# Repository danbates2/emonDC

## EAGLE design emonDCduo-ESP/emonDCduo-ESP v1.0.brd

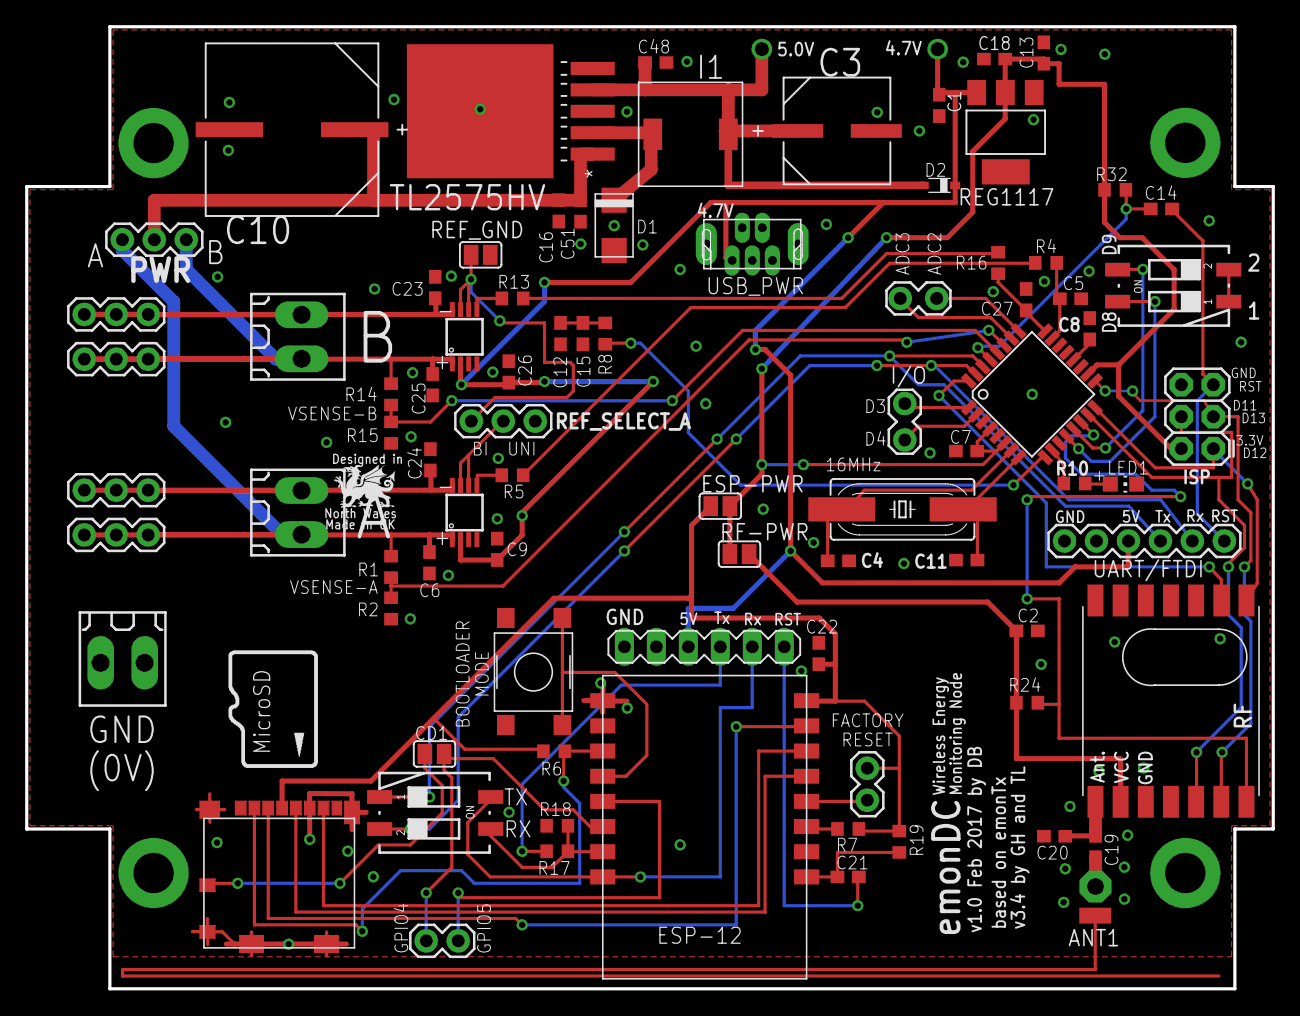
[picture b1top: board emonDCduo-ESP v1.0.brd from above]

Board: 2 copper layers, 99.1 x 76.5 mm, 85 parts (1 on the bottom side), 60 nets.

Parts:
ANA: 2212S-02SG-85; 1X02_LOCK
ANT1: PAD-01
C1, C18: 10uF TANT; C0603
C2, C5, C7, C8, C9, C12, C13, C14, C15, C21, C22, C26, C27, C48: 100nF; C0603
C3: 470uF 16V; CAPAE830X1050N
C4, C11, C19: 22pF; C0603
C6, C16, C23, C24, C25, C51: 0.1uF 100V; C0603
C10: 100uF 80V; CAPAE1350X1400N
C20: tune; C0603
CD1: SJ
D1: MBRA130LT3G; DO-214
D2: BAT60J; SOD323_ST
ESP-12: ESP8266_ESP-12; ESP8266-ESP12
ESP-PWR: SJ
FTDI1: FTDI-ESP; MA06-1
FTDI/UART: 2211S-06G; FTDI_BASIC
I1: 330uH; SRR0603-331KL
I/O: 2212S-02SG-85; 1X02_LOCK
IO1, IO2: 1X02
ISP: M20-9980346; 2X3
J1, J2, J3, J4: 1X03
LED1: Red 1.85V; CHIP-LED0805
LOGO1: OSHW_LOGO_6MILX0200-NT; OSHW_6X200_NOTEXT
MC2: MC32882; SWITCH_TACT_MULTICOMP
MINI_USB-B: 5000751517_SD
PAD1: SMD1,27-2,54
PWR: 1X03
Q1: 16Mhz XT49M-2016M; HC49UP
R1, R14: 100K 75V; R0603
R2, R15, R17: 5.6K; R0603
R4, R16: 9K1; R0603
R5, R10, R13: 1K; R0603
R6, R7, R18, R19: 10K; R0603
R8: 3.9K; R0603
R24: 120K; R0603
R32: 10k; R0603
REF_GND: SJ
REF_SELECT_A: 2212S-02SG-85; 1X03
REG1117: REG1117-3.3V; SOT223
RF: RFM12B
RF-PWR: SJ
S1, S3: A6S-2104-PH; DIP_SWITCH_SMT
SHUNTMON-A: LMP8481; S-PDSO-G08
SHUNTMON-B: LMP8481; S-PDSO-G08
T1, T2, T3: 180-2
TL2575HV: TL2575HV-5V; TO-263
U1_TQFP: ATMEGA328P; TQFP32-08
U$2: MOLEX_MICRO_SD_1040310811; MOLEX_MICROSD_EXPOSED

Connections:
3.3V: C7.1, C13.1, C18.1, ESP-PWR.2, ISP.2, R32.2, REG1117.2, RF-PWR.1, U1_TQFP.4, U1_TQFP.6, U1_TQFP.18
3.3V-ESP: C22.2, ESP-12.16, ESP-PWR.1, IO1.2, R6.2, R7.2, R19.2, U$2.P$4
3.3V-RF: C2.1, R24.2, RF.VDD, RF-PWR.2
4.7V: C1.1, C9.1, C26.1, D2.C, FTDI1.4, FTDI/UART.VCC, MINI_USB-B.VBUS, REG1117.3, SHUNTMON-A.2, SHUNTMON-B.2
5.0V: C3.1, C48.1, D2.A, I1.P$2, TL2575HV.4
ADC0: C5.2, R4.1, U1_TQFP.23
ADC1: C27.2, R16.1, U1_TQFP.24
ADC2: ANA.1, U1_TQFP.25
ADC3: ANA.2, U1_TQFP.26
ADC4-VSENSEA: R1.1, R2.2, U1_TQFP.27
ADC5-VSENSEB: R14.1, R15.2, U1_TQFP.28
ADCSHUNT-A: R4.2, R5.2
ADCSHUNT-B: R13.2, R16.2
CH_PD: ESP-12.11, R7.1
D0/RX: FTDI/UART.TXO, S1.1, U1_TQFP.30
D1/TX: FTDI/UART.RXI, S1.2, U1_TQFP.31
D2: RF.IRQ, U1_TQFP.32
D3: I/O.1, U1_TQFP.1
D4: I/O.2, U1_TQFP.2
D5/PWM0: R8.2, U1_TQFP.9
D6: R10.2, U1_TQFP.10
D8: S3.4, U1_TQFP.12
D9: S3.3, U1_TQFP.13
D10: R24.1, RF.SEL, U1_TQFP.14
D11/MOSI: ISP.4, RF.SDI, U1_TQFP.15
D12/MISO: ISP.1, RF.SDO, U1_TQFP.16
D13/SCK: ISP.3, RF.SCK, U1_TQFP.17
DIG1: C19.1, C20.1, RF.ANT
ESPRX: ESP-12.7, R17.2, R18.1, S1.3
ESPTX: ESP-12.8, FTDI1.2, S1.4
GND: C1.2, C2.2, C3.2, C4.2, C5.1, C6.2, C7.2, C8.2, C9.2, C10.2, C11.2, C12.2, C13.2, C15.2, C16.2, C18.2, C20.2, C22.1, C23.1, C24.1, C25.2, C26.2, C27.1, C48.2, C51.2, D1.P$2, ESP-12.1, ESP-12.2, FTDI1.6, FTDI/UART.GND, ISP.6, LED1.C, MC2.P$1, MC2.P$2, MINI_USB-B.GND1, MINI_USB-B.GND2, MINI_USB-B.GND3, R2.1, R15.1, R18.2, REF_GND.2, REF_SELECT_A.3, REG1117.1, RF.GND, RF.P$12, S3.1, S3.2, SHUNTMON-A.4, SHUNTMON-B.4, T3.1, T3.2, TL2575HV.3, TL2575HV.5, TL2575HV.6, U1_TQFP.3, U1_TQFP.5, U$2.CD2, U$2.GND1, U$2.GND2, U$2.GND3, U$2.GND4, U$2.P$6
GPIO0: ESP-12.4, MC2.P$3, MC2.P$4
GPIO2: ESP-12.3, R6.1, U$2.P$2
GPIO4: CD1.2, ESP-12.6, IO2.1
GPIO5: ESP-12.5, IO2.2
GPIO12: ESP-12.14, U$2.P$7
GPIO13: ESP-12.15, U$2.P$3
GPIO14: ESP-12.13, U$2.P$5
GPIO16: ESP-12.12, IO1.1
IND: D1.P$1, I1.P$1, TL2575HV.2
LOAD-NEG-A: C24.2, J4.1, J4.2, J4.3, SHUNTMON-B.8, T2.1
LOAD-NEG-B: C23.2, J1.1, J1.2, J1.3, SHUNTMON-A.8, T1.1
unnamed: C4.1, Q1.2, U1_TQFP.7
unnamed: ANT1.1, C19.2
unnamed: R13.1, SHUNTMON-A.5
unnamed: R5.1, SHUNTMON-B.5
unnamed: C11.1, Q1.1, U1_TQFP.8
unnamed: CD1.1, U$2.CD1
unnamed: REF_SELECT_A.2, SHUNTMON-B.6, SHUNTMON-B.7
unnamed: C8.1, U1_TQFP.20
unnamed: C21.2, FTDI1.1
unnamed: FTDI1.3, R17.1
unnamed: LED1.A, R10.1
PWR_IN: C10.1, C16.1, C51.1, PWR.2, TL2575HV.1
REFINPUT: C12.1, C15.1, R8.1, REF_GND.1, REF_SELECT_A.1, SHUNTMON-A.6, SHUNTMON-A.7
RESET1: C14.2, FTDI/UART.DTR, ISP.5
RESET2: C14.1, R32.1, U1_TQFP.29
RESTESP: C21.1, ESP-12.9, R19.1
SOURCE-POS-A: C6.1, J3.1, J3.2, J3.3, PWR.1, R1.2, SHUNTMON-B.1, T2.2
SOURCE-POS-B: C25.1, J2.1, J2.2, J2.3, PWR.3, R14.2, SHUNTMON-A.1, T1.2

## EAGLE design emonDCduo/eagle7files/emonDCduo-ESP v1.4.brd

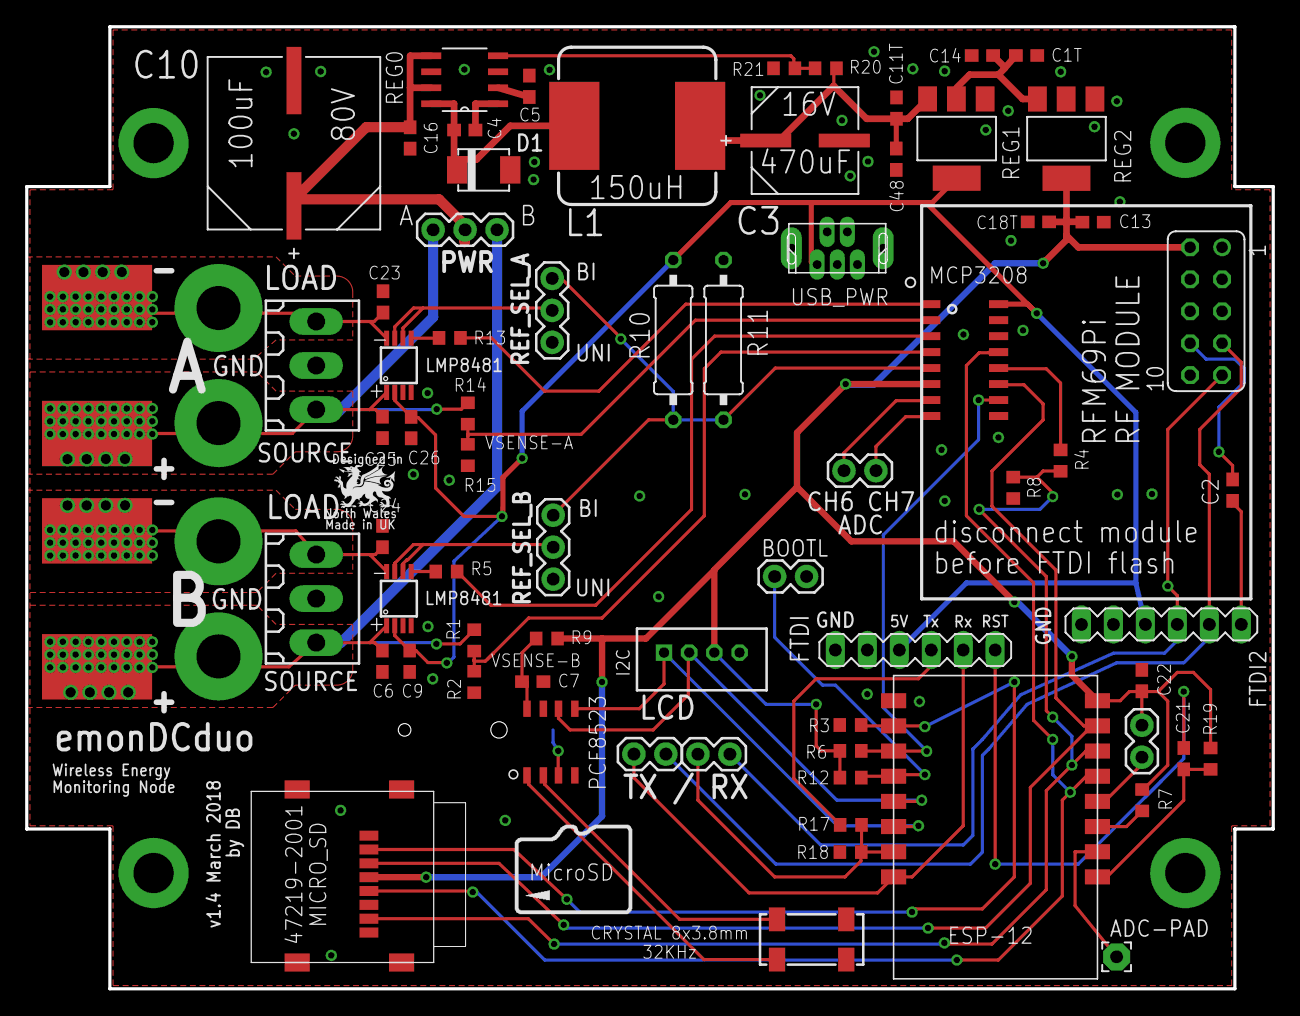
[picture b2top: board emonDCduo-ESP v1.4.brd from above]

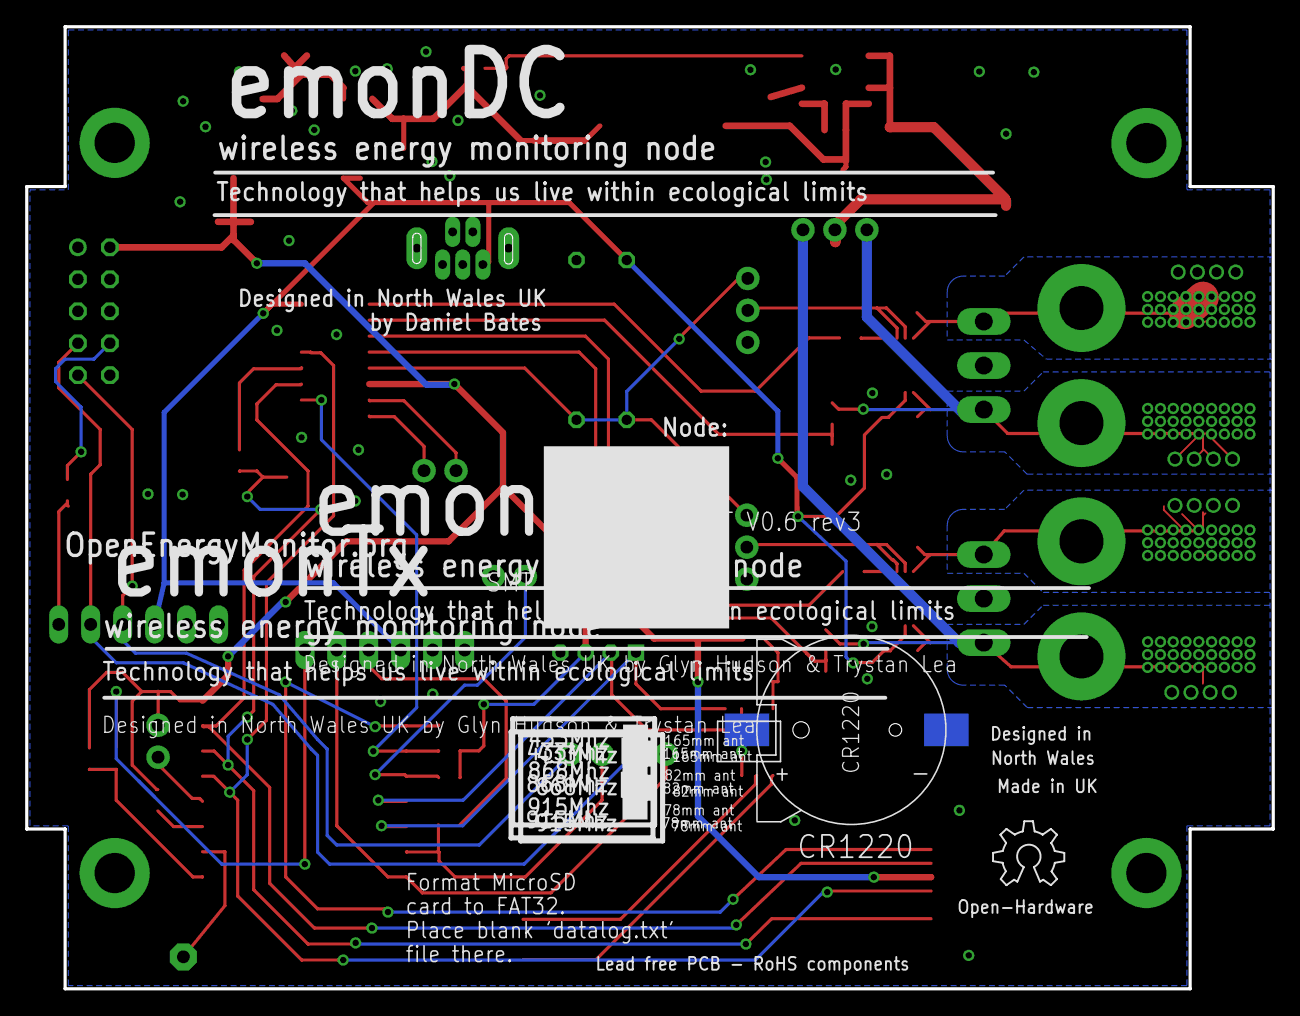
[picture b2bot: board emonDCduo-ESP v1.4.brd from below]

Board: 2 copper layers, 99.1 x 76.5 mm, 73 parts (2 on the bottom side), 49 nets.

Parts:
ADC-PAD: 2,15/1,0
BOOTL: 1X02
C1T, C11T, C18T: 10uF TANT; C0603
C2, C9, C21, C22, C26: 100nF; C0603
C3: 470uF 16V; CAPAE830X1050N
C4, C5: 0.1uF 16V MLCC; C0603
C6, C16, C23, C24, C25: 0.1uF 100V; C0603
C7: 10uF; C0603
C10: 100uF 80V (LOW-ESR); CAPAE1350X1400N
C13, C14: 0.1uF; C0603
C48: 0.1uF MLCC; C0603
CR1220: CR1220SMD
D1: MBRS1100T3G; SMB_1
ESP-12: ESP8266_ESP-12; ESP8266-ESP12
FTDI1, FTDI2: FTDI; MA06-1
GPIO_1: FE05-2
IO1: 1X02
J5: 455-1750-1-ND; 1X02
L1: SRR1208; SSR1208
LOGO1: OSHW_LOGO_6MILX0200-NT; OSHW_6X200_NOTEXT
MCP3208: MCP3208-BI/SL; SOIC16
P1: B4B-PH-K
PCF8523: PCF8523_RTC; SOIC_8
PWR: 455-1750-1-ND; 1X03
R1, R14: 100K 75V; R0603
R2, R15, R17: 5.6K; R0603
R3, R6, R7, R12, R18, R19: 10K; R0603
R4, R5, R9, R13: 1K; R0603
R8: 2K; R0603
R10: 10K; 0309/12
R11: 3.16K; 0309/12
R20: 57.6k; R0603
R21: 13.3k; R0603
REF_SEL_A: 455-1750-1-ND; 1X03
REF_SEL_B: 455-1750-1-ND; 1X03
REG0: MAX5035; 21-0111D_SBE-14
REG1: REG1117-5.0V; SOT223
REG2: REG1117-3.3V; SOT223
RX: 1X02
SCREW1, SCREW2: 180-3
SCREW_TERM_1, SCREW_TERM_2: EBW_SERIES_15.2MM
SHUNTMON-A: LMP8481; S-PDSO-G08
SHUNTMON-B: LMP8481; S-PDSO-G08
TX: 1X02
U$4: 47219-2001_MICROSD
USB_PWR: 5000751517_SD
Y1: 32Khz; CRYSTAL_8X3.8

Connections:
3.3V: C13.1, C18T.1, C22.2, ESP-12.16, GPIO_1.2, IO1.2, MCP3208.6, P1.3, R6.2, R7.2, R9.2, R12.2, R19.2, REG2.2, REG2.4, U$4.PIN4
5.0V: C1T.1, C9.1, C14.1, C26.1, FTDI1.4, FTDI2.4, MCP3208.16, R10.2, REG1.2, REG1.4, REG2.3, SHUNTMON-A.2, SHUNTMON-B.2, USB_PWR.VBUS
6.5V: C3.1, C11T.1, C48.1, L1.2, R20.2, REG1.3
ADC: ADC-PAD.1, ESP-12.10
ADCSHUNT-A: MCP3208.1, R13.2
ADCSHUNT-B: MCP3208.3, R5.2
BST: C4.1, REG0.1
CH6: J5.2, MCP3208.7
CH7: J5.1, MCP3208.8
CH_PD: ESP-12.11, R7.1
D0/RX: FTDI2.2, GPIO_1.7, TX.2
D1/TX: FTDI2.3, GPIO_1.9, RX.1
ESPRX: ESP-12.7, R17.2, R18.1, RX.2
ESPTX: ESP-12.8, FTDI1.2, TX.1
FB: R20.1, R21.2, REG0.4
GND: BOOTL.1, C1T.2, C3.2, C5.2, C6.2, C7.2, C9.2, C10.2, C11T.2, C13.2, C14.2, C16.2, C18T.2, C22.1, C23.1, C24.1, C25.2, C26.2, C48.2, CR1220.P-, D1.A, ESP-12.1, FTDI1.6, FTDI2.6, GPIO_1.5, GPIO_1.10, MCP3208.9, MCP3208.14, MCP3208.15, P1.4, PCF8523.4, R2.1, R3.2, R8.1, R11.1, R15.1, R18.2, R21.1, REF_SEL_A.1, REF_SEL_B.1, REG0.3, REG0.6, REG1.1, REG2.1, SCREW1.2, SCREW2.2, SHUNTMON-A.4, SHUNTMON-B.4, U$4.P$1, U$4.P$2, U$4.P$3, U$4.P$4, U$4.PIN6, USB_PWR.GND1, USB_PWR.GND2, USB_PWR.GND3
GPIO0: BOOTL.2, ESP-12.4, R12.1
GPIO2: ESP-12.3, MCP3208.10, R6.1
GPIO12: ESP-12.14, R4.1, R8.2, U$4.PIN7
GPIO12A: MCP3208.12, R4.2
GPIO13: ESP-12.15, MCP3208.11, U$4.PIN3
GPIO14: ESP-12.13, MCP3208.13, U$4.PIN5
GPIO15: ESP-12.2, R3.1, U$4.PIN2
GPIO16: ESP-12.12, IO1.1
LOAD-NEG-A: C23.2, SCREW1.1, SCREW_TERM_1.P$2, SHUNTMON-A.8
LOAD-NEG-B: C24.2, SCREW2.1, SCREW_TERM_2.P$2, SHUNTMON-B.8
LX: C4.2, D1.C, L1.1, REG0.8
unnamed: R13.1, SHUNTMON-A.5
unnamed: R5.1, SHUNTMON-B.5
unnamed: C7.1, PCF8523.8, R9.1
unnamed: C21.2, FTDI1.1
unnamed: FTDI1.3, R17.1
unnamed: CR1220.P+, PCF8523.3
unnamed: PCF8523.2, Y1.P$4
unnamed: PCF8523.1, Y1.P$1
unnamed: C2.2, FTDI2.1
REF_A_INPUT: REF_SEL_A.2, SHUNTMON-A.6, SHUNTMON-A.7
REF_B_INPUT: REF_SEL_B.2, SHUNTMON-B.6, SHUNTMON-B.7
REF_INPUT: MCP3208.5, R10.1, R11.2, REF_SEL_A.3, REF_SEL_B.3
RESTESP: C21.1, ESP-12.9, R19.1
SCL: ESP-12.5, P1.2, PCF8523.6
SDA: ESP-12.6, P1.1, PCF8523.5
SOURCE-POS-A: C25.1, PWR.3, R14.2, SCREW1.3, SCREW_TERM_1.P$1, SHUNTMON-A.1
SOURCE-POS-B: C6.1, PWR.1, R1.2, SCREW2.3, SCREW_TERM_2.P$1, SHUNTMON-B.1
VD: C5.1, REG0.2
VSENSEA: MCP3208.2, R14.1, R15.2
VSENSEB: MCP3208.4, R1.1, R2.2
V_IN: C10.1, C16.1, PWR.2, REG0.5, REG0.7
_RESET: C2.1, GPIO_1.8

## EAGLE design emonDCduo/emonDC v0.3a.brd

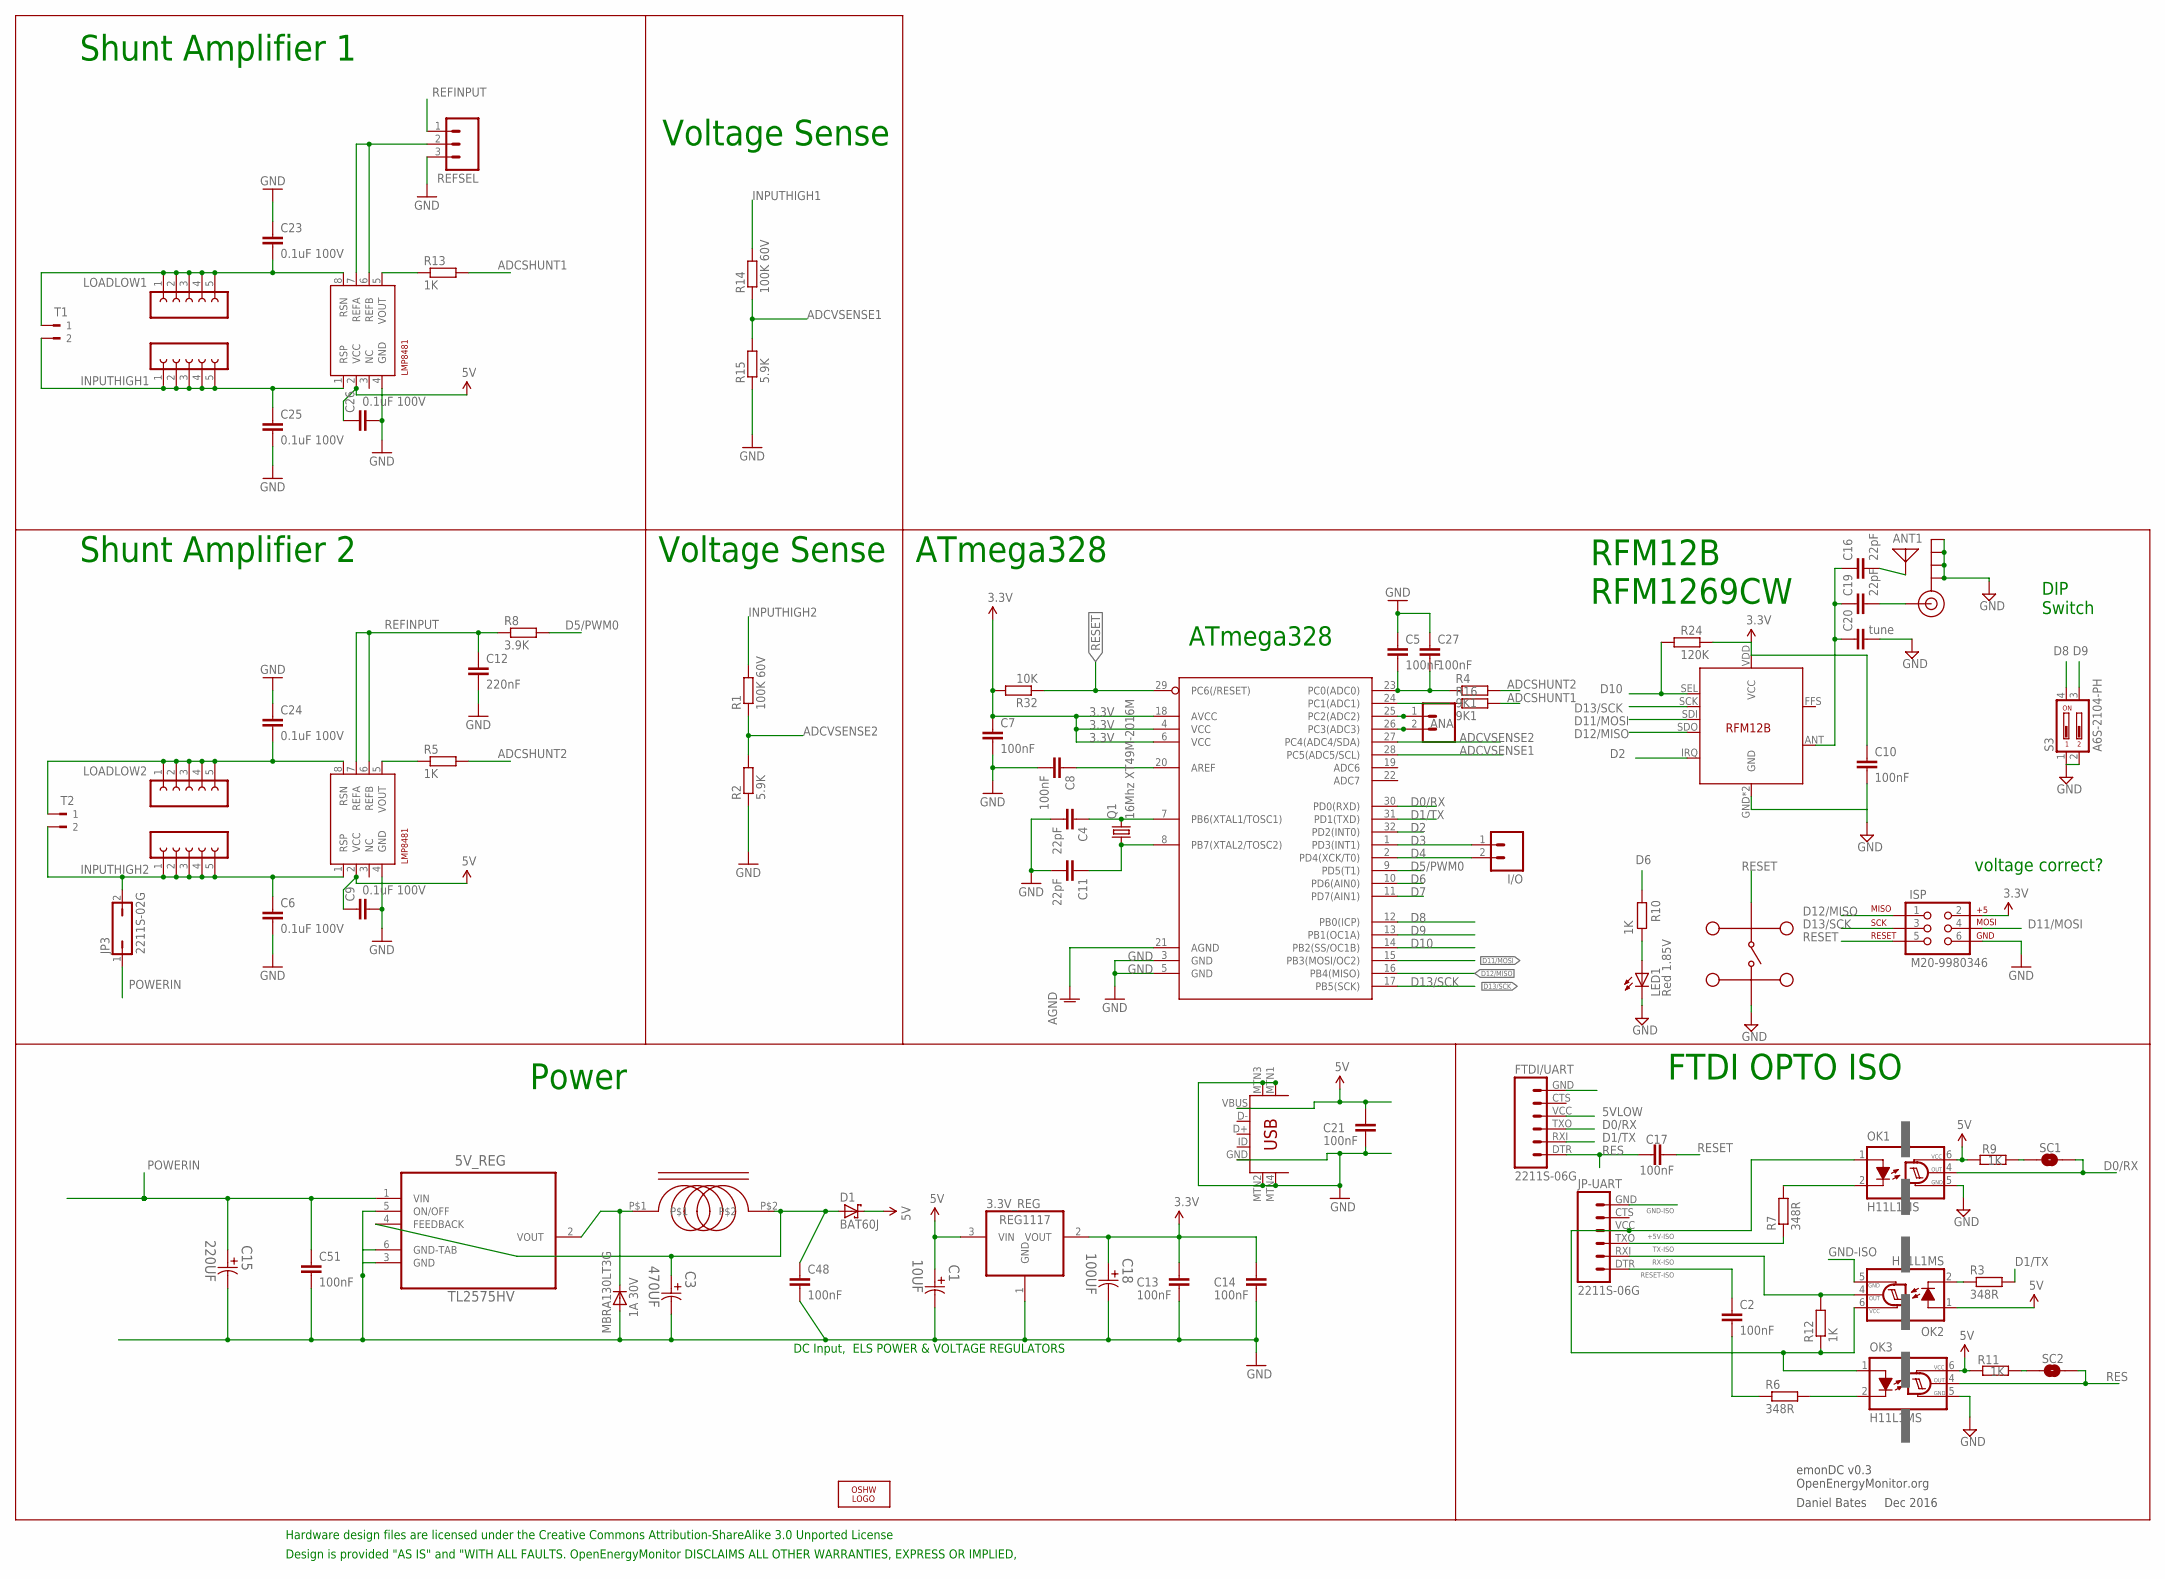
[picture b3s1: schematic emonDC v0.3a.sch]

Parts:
3.3V_REG: REG1117; SOT223
5V_REG: TL2575HV; TO-263; MPN LM2575HVS-15/NOPB
ANA: 2212S-02SG-85; 1X02_LOCK; MPN 2212S-02SG-85
ANT1: ANTENNA; PAD-01
C1: 10UF; CAPAE430X610N
C2, C5, C7, C8, C10, C13, C14, C17, C21, C27, C48, C51: 100nF; C0603
C3: 470UF; CAPAE830X1050N
C4, C11, C16, C19: 22pF; C0603
C6, C9, C23, C24, C25, C26: 0.1uF 100V; C0603; MPN C1608X7S2A104K080AB
C12: 220nF; C0603
C15: 220UF; CAPAE1350X1400N
C18: 100UF; CAPAE430X610N
C20: tune; C0603
D1: BAT60J; SOD323_ST
D2: MBRA130LT3G; DO-214; MPN MBRA130LT3G
FTDI/UART: 2211S-06G; FTDI_BASIC; MPN 2211S-06G
I1: SRR0603-331KL; MPN SRR0603-331KL
I/O: 2212S-02SG-85; 1X02_LOCK; MPN 2212S-02SG-85
ISP: M20-9980346; 2X3; MPN M20-9980346
J$1: SMA_EDGE; SMA-EDGE
JP3: 2211S-02G; JP1; MPN 2211S-02G
JP-LOAD, JP-LOAD1: 2212S-06SG-85; FE05-1; MPN 2212S-06SG-85
JP-SOURCE, JP-SOURCE1: 2212S-06SG-85; FE05-1; MPN 2212S-06SG-85
JP-UART: 2211S-06G; FTDI_BASIC; MPN 2211S-06G
LED1: Red 1.85V; CHIP-LED0805; MPN SML-211UTT86K
LMP1: LMP8481LMP8481-H; S-PDSO-G08; MPN LMP8481MME-S/NOPB
LMP8481: LMP8481-H; S-PDSO-G08; MPN LMP8481MME-H/NOPB
LOGO1: OSHW_LOGO_6MILX0200-NT; OSHW_6X200_NOTEXT
MC32882: MC32882; SWITCH_TACT_MULTICOMP
OK1, OK2, OK3: H11L1MS; DIL6-SMD
Q1: 16Mhz XT49M-2016M; HC49UP; MPN XT49M-2016M
R1, R14: 100K 60V; R0603; MPN MCWR06X1003FTL
R2, R15: 5.9K; R0603; MPN MCWR06X5901FTL
R3, R6, R7: 348R; R0603
R4, R16: 9K1; R0603
R5, R9, R10, R11, R12, R13: 1K; R0603
R8: 3.9K; R0603
R24: 120K; R0603
R32: 10K; R0603
REFSEL: 2212S-02SG-85; 1X03; MPN 2212S-02SG-85
RF: RFM12B
S3: A6S-2104-PH; DIP_SWITCH_SMT; MPN A6S2104H
SC1, SC2: SOLDERJUMPERNO; SJ_2S-NO
T1, T2: 180-2
U1_TQFP: ATMEGA328P; TQFP32-08; MPN ATMEGA328-AU
USB: MUSB-05-S-B-SM-A; USB-MINIB-CISECO; MPN 67503-1020

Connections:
3.3V: 3.3V_REG.2 (VOUT), C7.1, C10.1, C13.1, C14.1, C18.1, ISP.2, R24.2, R32.2, RF.VDD (VCC), U1_TQFP.4 (VCC), U1_TQFP.6 (VCC), U1_TQFP.18 (AVCC)
5VHIGH: 5V_REG.4 (FEEDBACK), C3.1, C48.1, D1.A, I1.P$2
5VLOW: 3.3V_REG.3 (VIN), C1.1, C9.1, C21.1, C26.1, D1.C, FTDI/UART.VCC (4), LMP1.2 (VCC), LMP8481.2 (VCC), OK1.6 (VCC), OK2.1 (A), OK3.6 (VCC), R9.2, R11.2, USB.VBUS
+5V-ISO: JP-UART.VCC (4), OK1.1 (A), OK2.6 (VCC), OK3.1 (A), R12.1
ADCSHUNT1: R13.2, R16.2
ADCSHUNT2: R4.2, R5.2
ADCVSENSE1: R14.1, R15.2, U1_TQFP.28 (PC5(ADC5/SCL))
ADCVSENSE2: R1.1, R2.2, U1_TQFP.27 (PC4(ADC4/SDA))
AGND: U1_TQFP.21 (AGND)
D0/RX: FTDI/UART.TXO (3), OK1.4 (OUT), SC1.1, U1_TQFP.30 (PD0(RXD))
D1/TX: FTDI/UART.RXI (2), R3.2, U1_TQFP.31 (PD1(TXD))
D2: RF.IRQ, U1_TQFP.32 (PD2(INT0))
D3: I/O.1, U1_TQFP.1 (PD3(INT1))
D4: I/O.2, U1_TQFP.2 (PD4(XCK/T0))
D5/PWM0: R8.2, U1_TQFP.9 (PD5(T1))
D6: R10.2, U1_TQFP.10 (PD6(AIN0))
D7: U1_TQFP.11 (PD7(AIN1))
D8: S3.4, U1_TQFP.12 (PB0(ICP))
D9: S3.3, U1_TQFP.13 (PB1(OC1A))
D10: R24.1, RF.SEL, U1_TQFP.14 (PB2(SS/OC1B))
D11/MOSI: ISP.4, RF.SDI, U1_TQFP.15 (PB3(MOSI/OC2))
D12/MISO: ISP.1, RF.SDO, U1_TQFP.16 (PB4(MISO))
D13/SCK: ISP.3, RF.SCK, U1_TQFP.17 (PB5(SCK))
DIG1: C16.1, C19.1, C20.1, RF.ANT
GND: 3.3V_REG.1 (GND), 5V_REG.3 (GND), 5V_REG.5 (ON/OFF), 5V_REG.6 (GND-TAB), C1.2, C3.2, C4.2, C5.1, C6.2, C7.2, C8.2, C9.2, C10.2, C11.2, C12.2, C13.2, C14.2, C15.2, C18.2, C20.2, C21.2, C23.1, C24.1, C25.2, C26.2, C27.1, C48.2, C51.2, D2.P$2 (A), FTDI/UART.GND (6), ISP.6, J$1.GND@0 (GND), J$1.GND@1 (GND), J$1.GND@2 (GND), J$1.GND@3 (GND), LED1.C, LMP1.4 (GND), LMP8481.4 (GND), MC32882.P$3, MC32882.P$4, OK1.5 (GND), OK3.5 (GND), R2.1, R15.1, REFSEL.3, RF.GND, RF.P$12 (GND), S3.1, S3.2, U1_TQFP.3 (GND), U1_TQFP.5 (GND), USB.GND, USB.MTN1 (MTN2), USB.MTN2 (MTN3), USB.MTN3 (MTN1), USB.MTN4
GND-ISO: JP-UART.GND (6), OK2.5 (GND)
IND: 5V_REG.2 (VOUT), D2.P$1 (C), I1.P$1
INPUTHIGH1: C25.1, JP-LOAD1.1, JP-LOAD1.2, JP-LOAD1.3, JP-LOAD1.4, JP-LOAD1.5, LMP1.1 (RSP), R14.2, T1.2
INPUTHIGH2: C6.1, JP3.2, JP-LOAD.1, JP-LOAD.2, JP-LOAD.3, JP-LOAD.4, JP-LOAD.5, LMP8481.1 (RSP), R1.2, T2.2
LOADLOW1: C23.2, JP-SOURCE1.1, JP-SOURCE1.2, JP-SOURCE1.3, JP-SOURCE1.4, JP-SOURCE1.5, LMP1.8 (RSN), T1.1
LOADLOW2: C24.2, JP-SOURCE.1, JP-SOURCE.2, JP-SOURCE.3, JP-SOURCE.4, JP-SOURCE.5, LMP8481.8 (RSN), T2.1
unnamed: C4.1, Q1.2, U1_TQFP.7 (PB6(XTAL1/TOSC1))
unnamed: C5.2, C27.2, R4.1, U1_TQFP.23 (PC0(ADC0))
unnamed: R11.1, SC2.2
unnamed: LMP1.5 (VOUT), R13.1
unnamed: R9.1, SC1.2
unnamed: LMP8481.5 (VOUT), R5.1
unnamed: C11.1, Q1.1, U1_TQFP.8 (PB7(XTAL2/TOSC2))
unnamed: C2.1, JP-UART.DTR (1)
unnamed: ANT1.1, C16.2
unnamed: OK1.2 (C), R7.2
unnamed: OK2.2 (C), R3.1
unnamed: OK3.2 (C), R6.2
unnamed: C8.1, U1_TQFP.20 (AREF)
unnamed: ANA.2, U1_TQFP.26 (PC3(ADC3))
unnamed: ANA.1, U1_TQFP.25 (PC2(ADC2))
unnamed: C19.2, J$1.SIG (SIGNAL)
unnamed: R16.1, U1_TQFP.24 (PC1(ADC1))
unnamed: LMP1.6 (REFB), LMP1.7 (REFA), REFSEL.2
unnamed: LED1.A, R10.1
POWERIN: 5V_REG.1 (VIN), C15.1, C51.1, JP3.1
REFINPUT: C12.1, LMP8481.6 (REFB), LMP8481.7 (REFA), R8.1, REFSEL.1
RES: C17.1, FTDI/UART.DTR (1), OK3.4 (OUT), SC2.1
RESET: C17.2, ISP.5, MC32882.P$1, MC32882.P$2, R32.1, U1_TQFP.29 (PC6(/RESET))
RESET-ISO: C2.2, R6.1
RX-ISO: JP-UART.RXI (2), OK2.4 (OUT), R12.2
TX-ISO: JP-UART.TXO (3), R7.1

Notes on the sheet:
emonDC v0.3 OpenEnergyMonitor.org
Daniel Bates Dec 2016
Power
ATmega328
Design is provided "AS IS" and "WITH ALL FAULTS. OpenEnergyMonitor DISCLAIMS ALL OTHER WARRANTIES, EXPRESS OR IMPLIED,
Hardware design files are licensed under the Creative Commons Attribution-ShareAlike 3.0 Unported License
RFM12B RFM1269CW
DIP Switch
FTDI OPTO ISO
DC Input, ELS POWER & VOLTAGE REGULATORS
Shunt Amplifier 2
voltage correct?
Voltage Sense
Shunt Amplifier 1

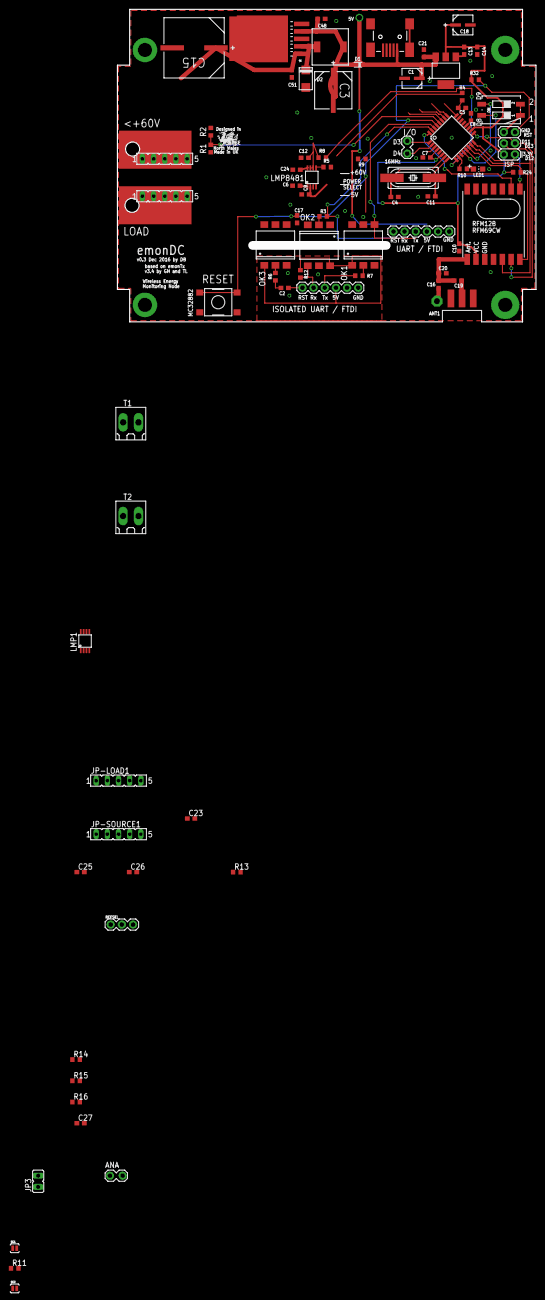
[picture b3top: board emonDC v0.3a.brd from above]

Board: 2 copper layers, 95.2 x 71.1 mm, 81 parts (1 on the bottom side), 55 nets.

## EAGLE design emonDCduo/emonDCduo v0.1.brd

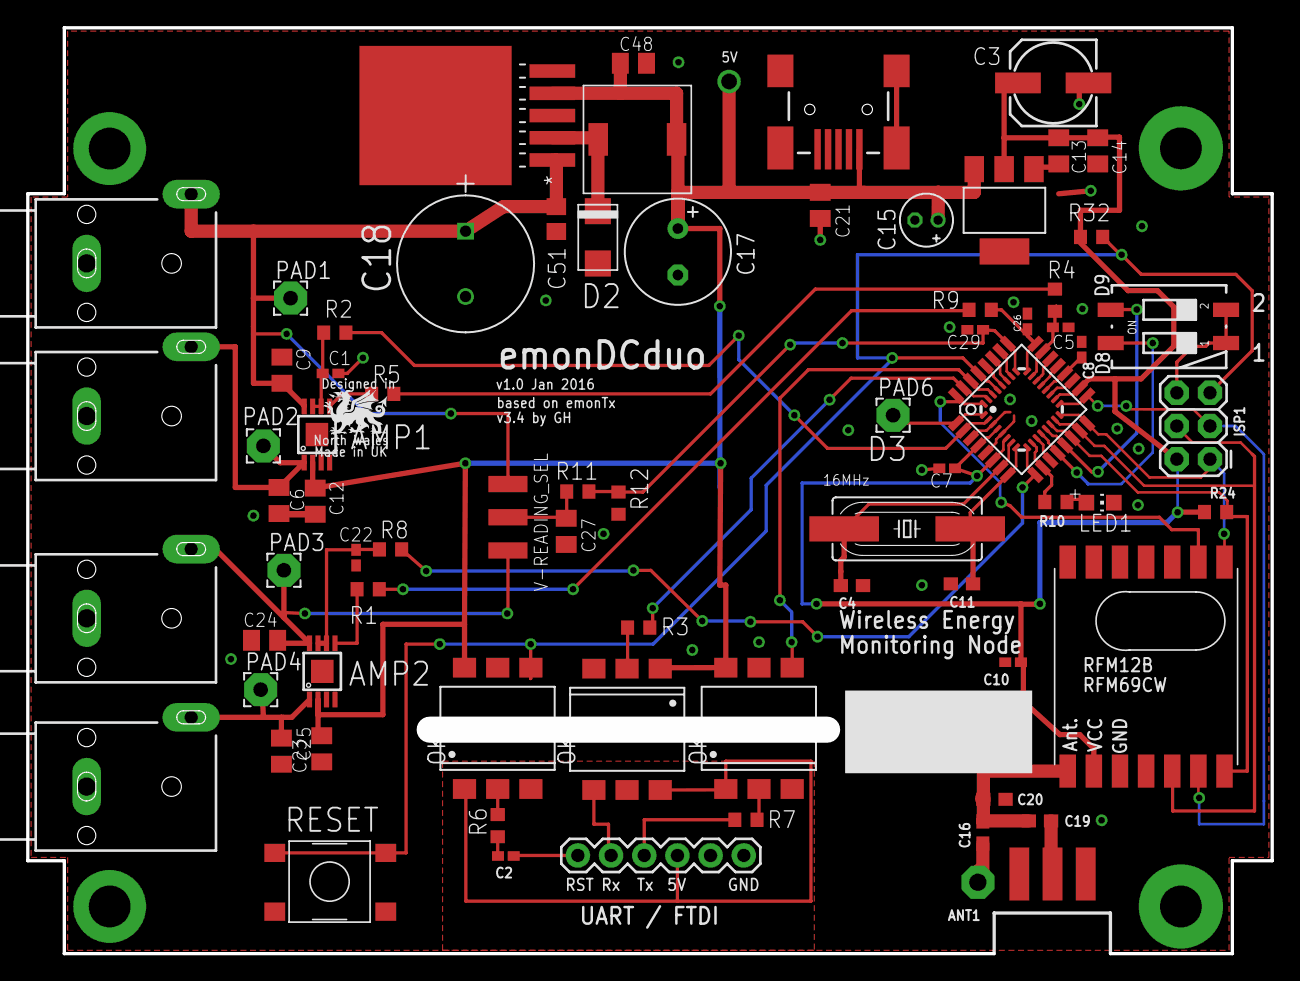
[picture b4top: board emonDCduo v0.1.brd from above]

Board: 2 copper layers, 95.2 x 70.9 mm, 76 parts (1 on the bottom side), 55 nets.

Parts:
3.3V_REG: REG1117; SOT223
5V_REG: TL2575HV; TO-263
ANT1: PAD-01
ATMEGA328: ATMEGA168MLF; MLF32
C1, C22: 0.22uF 6.3V; C0402K
C2, C5, C7, C8, C10, C26, C29: 100nF; C0402K
C3: 100uF; 153CLV-0605
C4, C11, C16, C19: 22pF; C0603
C6, C9, C12, C23, C24, C25, C27: 100nF 100V; C0805K
C13, C14, C21, C48: 0.1uF; C0805K
C15: 10uF 35v; E1,8-4
C17: 470uF 16V; E3,5-8
C18: 330UF 63V; CAPPR500-1000X2000
C20: tune; C0603
C51: 0.1uF; C0805
D2: MBRA130LT3G; DO-214
I1: SRR0603-331KL
ISP1: M20-9980346; 2X3
J$1: SMA_EDGE; SMA-EDGE
JP-UART: 2211S-06G; FTDI_BASIC
LED1: Red 1.85V; CHIP-LED0805
LMP2, LMP8481: LMP8481SMCLMP8481; S-PDSO-G08
LOGO1: OSHW_LOGO_6MILX0200-NT; OSHW_6X200_NOTEXT
OK1, OK2, OK3: H11L1MS; DIL6-SMD
PAD1, PAD2, PAD3, PAD4, PAD6: WIREPAD2,54/1,1; 2,54/1,1
Q1: 16Mhz XT49M-2016M; HC49UP
R1, R5, R10: 1K; R0603
R2, R8: 3.9K; R0603
R3, R6, R7: 348R; R0603
R4, R9, R12: 9K1; R0603
R11, R24: 120K; R0603
R32: 10K; R0603
RF: RFM12B
S3: A6S-2104-PH; DIP_SWITCH_SMT
U1_TQFP: ATMEGA328P; TQFP32-08
U$1: MC32882; SWITCH_TACT_MULTICOMP
USB: MUSB-05-S-B-SM-A; USB-MINIB-CISECO
V-READING_SEL: M20-9990346; 1X03_SMD_RA_FEMALE_NOWRITE
X1, X2, X3, X4: PSG01540; WBTOR1

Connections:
3.3V: 3.3V_REG.2, ATMEGA328.4, ATMEGA328.6, ATMEGA328.18, C3.+, C7.1, C10.1, C13.1, C14.1, ISP1.2, R24.2, R32.2, RF.VDD, U1_TQFP.4, U1_TQFP.6, U1_TQFP.18
5V: 3.3V_REG.3, 5V_REG.4, C12.2, C15.+, C17.+, C21.1, C25.2, C48.1, I1.P$2, LMP2.2, LMP8481.2, OK1.6, OK2.1, OK3.6, USB.VBUS
+5V-ISO: JP-UART.VCC, OK1.1, OK2.6, OK3.1
A6: ATMEGA328.19, U1_TQFP.19
A7: ATMEGA328.22, U1_TQFP.22
ACD2: ATMEGA328.25, C29.1, R11.1, R12.2, U1_TQFP.25
ADC0A: R4.2, R5.2
ADC1A: R1.2, R9.2
ADC1AYEA: ATMEGA328.24, C26.2, R9.1, U1_TQFP.24
ADC4: ATMEGA328.26, U1_TQFP.26
ADC5: ATMEGA328.28, U1_TQFP.28
AGND: ATMEGA328.21, U1_TQFP.21
D0/RX: ATMEGA328.30, OK1.4, U1_TQFP.30
D1/TX: ATMEGA328.31, R3.2, U1_TQFP.31
D2: ATMEGA328.32, RF.IRQ, U1_TQFP.32
D3: ATMEGA328.1, PAD6.1, U1_TQFP.1
D4/PWM0: ATMEGA328.2, R2.2, U1_TQFP.2
D5/PWM1: ATMEGA328.9, R8.2, U1_TQFP.9
D6: ATMEGA328.10, R10.2, U1_TQFP.10
D7: ATMEGA328.11, U1_TQFP.11
D8: ATMEGA328.12, S3.4, U1_TQFP.12
D9: ATMEGA328.13, S3.3, U1_TQFP.13
D10: ATMEGA328.14, R24.1, RF.SEL, U1_TQFP.14
D11/MOSI: ATMEGA328.15, ISP1.4, RF.SDI, U1_TQFP.15
D12/MISO: ATMEGA328.16, ISP1.1, RF.SDO, U1_TQFP.16
D13/SCK: ATMEGA328.17, ISP1.3, RF.SCK, U1_TQFP.17
DIG1: C16.1, C19.1, C20.1, RF.ANT
GND: 3.3V_REG.1, 5V_REG.3, 5V_REG.5, 5V_REG.6, ATMEGA328.3, ATMEGA328.5, C1.2, C3.-, C4.2, C5.1, C6.2, C7.2, C8.2, C9.1, C10.2, C11.2, C12.1, C13.2, C14.2, C15.-, C17.-, C18.2, C20.2, C21.2, C22.2, C23.2, C24.1, C25.1, C26.1, C27.2, C29.2, C48.2, C51.2, D2.P$2, ISP1.6, J$1.GND@0, J$1.GND@1, J$1.GND@2, J$1.GND@3, LED1.C, LMP2.4, LMP8481.4, OK1.5, OK3.5, R12.1, RF.GND, RF.P$12, S3.1, S3.2, U1_TQFP.3, U1_TQFP.5, U$1.P$3, U$1.P$4, USB.GND, USB.MTN1, USB.MTN2, USB.MTN3, USB.MTN4, X1.S, X2.S, X3.S, X4.S
GND-ISO: JP-UART.GND, OK2.5
IND: 5V_REG.2, D2.P$1, I1.P$1
INPUTLINE1: 5V_REG.1, C9.2, C18.1, C51.1, LMP8481.8, PAD1.1, V-READING_SEL.1, X1.T
INPUTLINE2: C24.2, LMP2.8, PAD3.1, V-READING_SEL.3, X4.T
unnamed: ATMEGA328.7, C4.1, Q1.2, U1_TQFP.7
unnamed: ATMEGA328.23, C5.2, R4.1, U1_TQFP.23
unnamed: LMP2.5, R1.1
unnamed: ATMEGA328.27, U1_TQFP.27
unnamed: LMP8481.5, R5.1
unnamed: ATMEGA328.8, C11.1, Q1.1, U1_TQFP.8
unnamed: C2.1, JP-UART.DTR
unnamed: ANT1.1, C16.2
unnamed: OK1.2, R7.2
unnamed: OK2.2, R3.1
unnamed: OK3.2, R6.2
unnamed: ATMEGA328.20, C8.1, U1_TQFP.20
unnamed: C19.2, J$1.SIG
unnamed: LED1.A, R10.1
NETDF: C22.1, LMP2.6, LMP2.7, R8.1
NETDG: C1.1, LMP8481.6, LMP8481.7, R2.1
RESET: ATMEGA328.29, ISP1.5, OK3.4, R32.1, U1_TQFP.29, U$1.P$1, U$1.P$2
RESET-ISO: C2.2, R6.1
RX-ISO: JP-UART.RXI, OK2.4
TOLOAD1: C6.1, LMP8481.1, PAD2.1, X2.T
TOLOAD2: C23.1, LMP2.1, PAD4.1, X3.T
TX-ISO: JP-UART.TXO, R7.1
VSEL: C27.1, R11.2, V-READING_SEL.2

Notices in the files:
parts and their libraries:
SparkFun-DigitalIC: Licensing: CC v3.0 Share-Alike You are welcome to use this library for commercial purposes.
microbuilder: This work is placed in the public domain, and may be freely used for commercial and non-commercial work with the following conditions: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
jst-ph: Copyright (C) 2016, Bob Starr
